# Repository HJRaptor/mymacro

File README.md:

# HackPad
## My experience
As part of **Hack Club’s HACKPAD YSWS** program, I embarked on a rewarding journey to build my own DIY macropad. This experience allowed me to explore various technical disciplines, from designing a custom **PCB in KiCAD** to **coding my very own firmware with QMK**. The most challenging aspect of the project was undoubtedly the PCB design. It required extensive research into component specifications, navigating datasheets, and ensuring that each part—switches, diodes, microcontrollers—was properly integrated into the design. The process of **placing components and routing the traces** was the most time-consuming and working through these challenges gave me a much deeper understanding of electronics design.

On the other hand, the part I enjoyed the most was **working with CAD**. With my existing CAD skills, I was able to confidently create a functional layout for the macropad’s physical structure. Translating these skills into real-world applications for a product I could use was fulfilling and rewarding. Coding the firmware was surprisingly straightforward, thanks to QMK's user-friendly environment, making the software side of things much simpler than anticipated. 
***Overall, this project was an invaluable learning experience that not only introduced me to PCB design but also allowed me to merge my existing skills with new knowledge to create something tangible and functional.***
## Bill Of Materials

    Xiao RP2040
    PCF8574 IO expander
    SSD1306 0.96 OLED
    (2) 4.7k resistor
    (16) SK6812 LED
    (16) 1N4148 diodes
    (16) Cherry MX brown switches

    (16) any keycaps at hq
    (16) Mill-Max 0305s hotswap socket
    (2) any encoder knobs at hq
    (2) EC11 encoder
    
    **--> Please laser cut the plate in 3mm clear acrylic and 3D print the rest of the pieces.**

### My Model

### My schematic

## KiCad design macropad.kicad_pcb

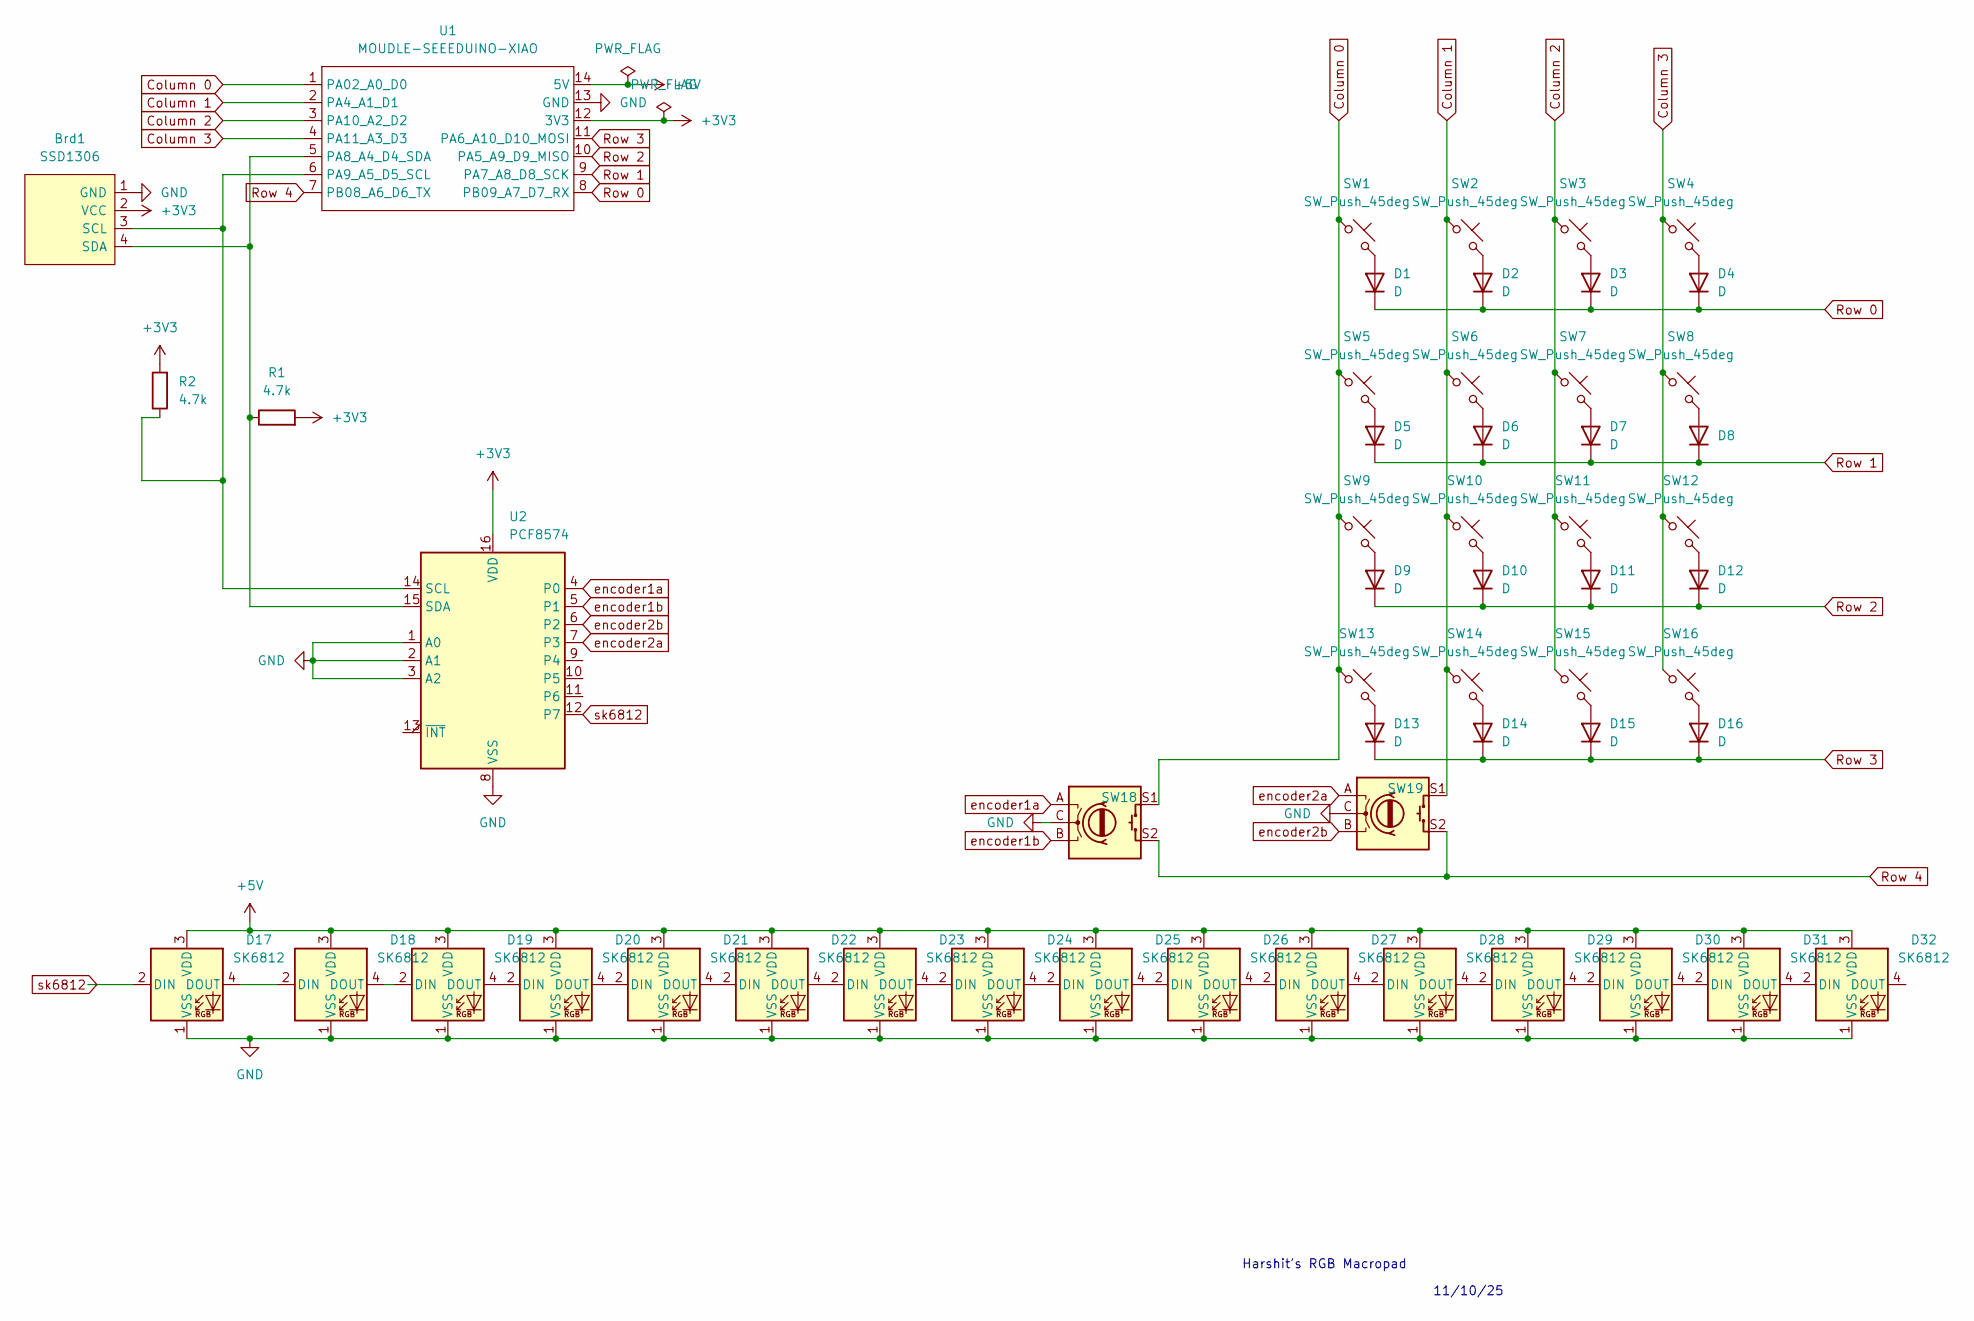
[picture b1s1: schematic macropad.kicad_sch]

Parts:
Brd1: SSD1306; SSD1306-0.91-OLED-4pin-128x32
D1, D2, D3, D4, D5, D6, D7, D8, D9, D10, D11, D12, D13, D14, D15, D16: D; D_DO-35_SOD27_P7.62mm_Horizontal
D17, D18, D19, D20, D21, D22, D23, D24, D25, D26, D27, D28, D29, D30, D31, D32: SK6812; LED_SK6812_PLCC4_5.0x5.0mm_P3.2mm
R1, R2: 4.7k; R_Axial_DIN0204_L3.6mm_D1.6mm_P5.08mm_Horizontal
SW1, SW2, SW3, SW4, SW5, SW6, SW7, SW8, SW9, SW10, SW11, SW12, SW13, SW14, SW15, SW16: SW_Push_45deg; SW_Cherry_MX_1.00u_PCB
SW18, SW19: RotaryEncoder_Switch; RotaryEncoder_Alps_EC11E-Switch_Vertical_H20mm
U1: MOUDLE-SEEEDUINO-XIAO; MOUDLE14P-2.54-21X17.8MM
U2: PCF8574; N16

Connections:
+3V3: Brd1.2 (VCC), R1.2, R2.2, U1.12 (3V3), U2.16 (VDD)
+5V: D17.3 (VDD), D18.3 (VDD), D19.3 (VDD), D20.3 (VDD), D21.3 (VDD), D22.3 (VDD), D23.3 (VDD), D24.3 (VDD), D25.3 (VDD), D26.3 (VDD), D27.3 (VDD), D28.3 (VDD), D29.3 (VDD), D30.3 (VDD), D31.3 (VDD), D32.3 (VDD), U1.14 (5V)
Column 0: SW1.1, SW5.1, SW9.1, SW13.1, SW18.S1, U1.1 (PA02_A0_D0)
Column 1: SW2.1, SW6.1, SW10.1, SW14.1, SW19.S1, U1.2 (PA4_A1_D1)
Column 2: SW3.1, SW7.1, SW11.1, SW15.1, U1.3 (PA10_A2_D2)
Column 3: SW4.1, SW8.1, SW12.1, SW16.1, U1.4 (PA11_A3_D3)
GND: Brd1.1 (GND), D17.1 (VSS), D18.1 (VSS), D19.1 (VSS), D20.1 (VSS), D21.1 (VSS), D22.1 (VSS), D23.1 (VSS), D24.1 (VSS), D25.1 (VSS), D26.1 (VSS), D27.1 (VSS), D28.1 (VSS), D29.1 (VSS), D30.1 (VSS), D31.1 (VSS), D32.1 (VSS), SW18.C, SW19.C, U1.13 (GND), U2.1 (A0), U2.2 (A1), U2.3 (A2), U2.8 (VSS)
unnamed: Brd1.3 (SCL), R2.1, U1.6 (PA9_A5_D5_SCL), U2.14 (SCL)
unnamed: Brd1.4 (SDA), R1.1, U1.5 (PA8_A4_D4_SDA), U2.15 (SDA)
unnamed: D1.2 (A), SW1.2
unnamed: D2.2 (A), SW2.2
unnamed: D3.2 (A), SW3.2
unnamed: D4.2 (A), SW4.2
unnamed: D5.2 (A), SW5.2
unnamed: D6.2 (A), SW6.2
unnamed: D7.2 (A), SW7.2
unnamed: D8.2 (A), SW8.2
unnamed: D9.2 (A), SW9.2
unnamed: D10.2 (A), SW10.2
unnamed: D11.2 (A), SW11.2
unnamed: D12.2 (A), SW12.2
unnamed: D13.2 (A), SW13.2
unnamed: D14.2 (A), SW14.2
unnamed: D15.2 (A), SW15.2
unnamed: D16.2 (A), SW16.2
unnamed: D17.4 (DOUT), D18.2 (DIN)
unnamed: D18.4 (DOUT), D19.2 (DIN)
unnamed: D19.4 (DOUT), D20.2 (DIN)
unnamed: D20.4 (DOUT), D21.2 (DIN)
unnamed: D21.4 (DOUT), D22.2 (DIN)
unnamed: D22.4 (DOUT), D23.2 (DIN)
unnamed: D23.4 (DOUT), D24.2 (DIN)
unnamed: D24.4 (DOUT), D25.2 (DIN)
unnamed: D25.4 (DOUT), D26.2 (DIN)
unnamed: D26.4 (DOUT), D27.2 (DIN)
unnamed: D27.4 (DOUT), D28.2 (DIN)
unnamed: D28.4 (DOUT), D29.2 (DIN)
unnamed: D29.4 (DOUT), D30.2 (DIN)
unnamed: D30.4 (DOUT), D31.2 (DIN)
unnamed: D31.4 (DOUT), D32.2 (DIN)
Row 0: D1.1 (K), D2.1 (K), D3.1 (K), D4.1 (K), U1.8 (PB09_A7_D7_RX)
Row 1: D5.1 (K), D6.1 (K), D7.1 (K), D8.1 (K), U1.9 (PA7_A8_D8_SCK)
Row 2: D9.1 (K), D10.1 (K), D11.1 (K), D12.1 (K), U1.10 (PA5_A9_D9_MISO)
Row 3: D13.1 (K), D14.1 (K), D15.1 (K), D16.1 (K), U1.11 (PA6_A10_D10_MOSI)
Row 4: SW18.S2, SW19.S2, U1.7 (PB08_A6_D6_TX)
encoder1a: SW18.A, U2.4 (P0)
encoder1b: SW18.B, U2.5 (P1)
encoder2a: SW19.A, U2.7 (P3)
encoder2b: SW19.B, U2.6 (P2)
sk6812: D17.2 (DIN), U2.12 (P7)

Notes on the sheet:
11/10/25
Harshit's RGB Macropad

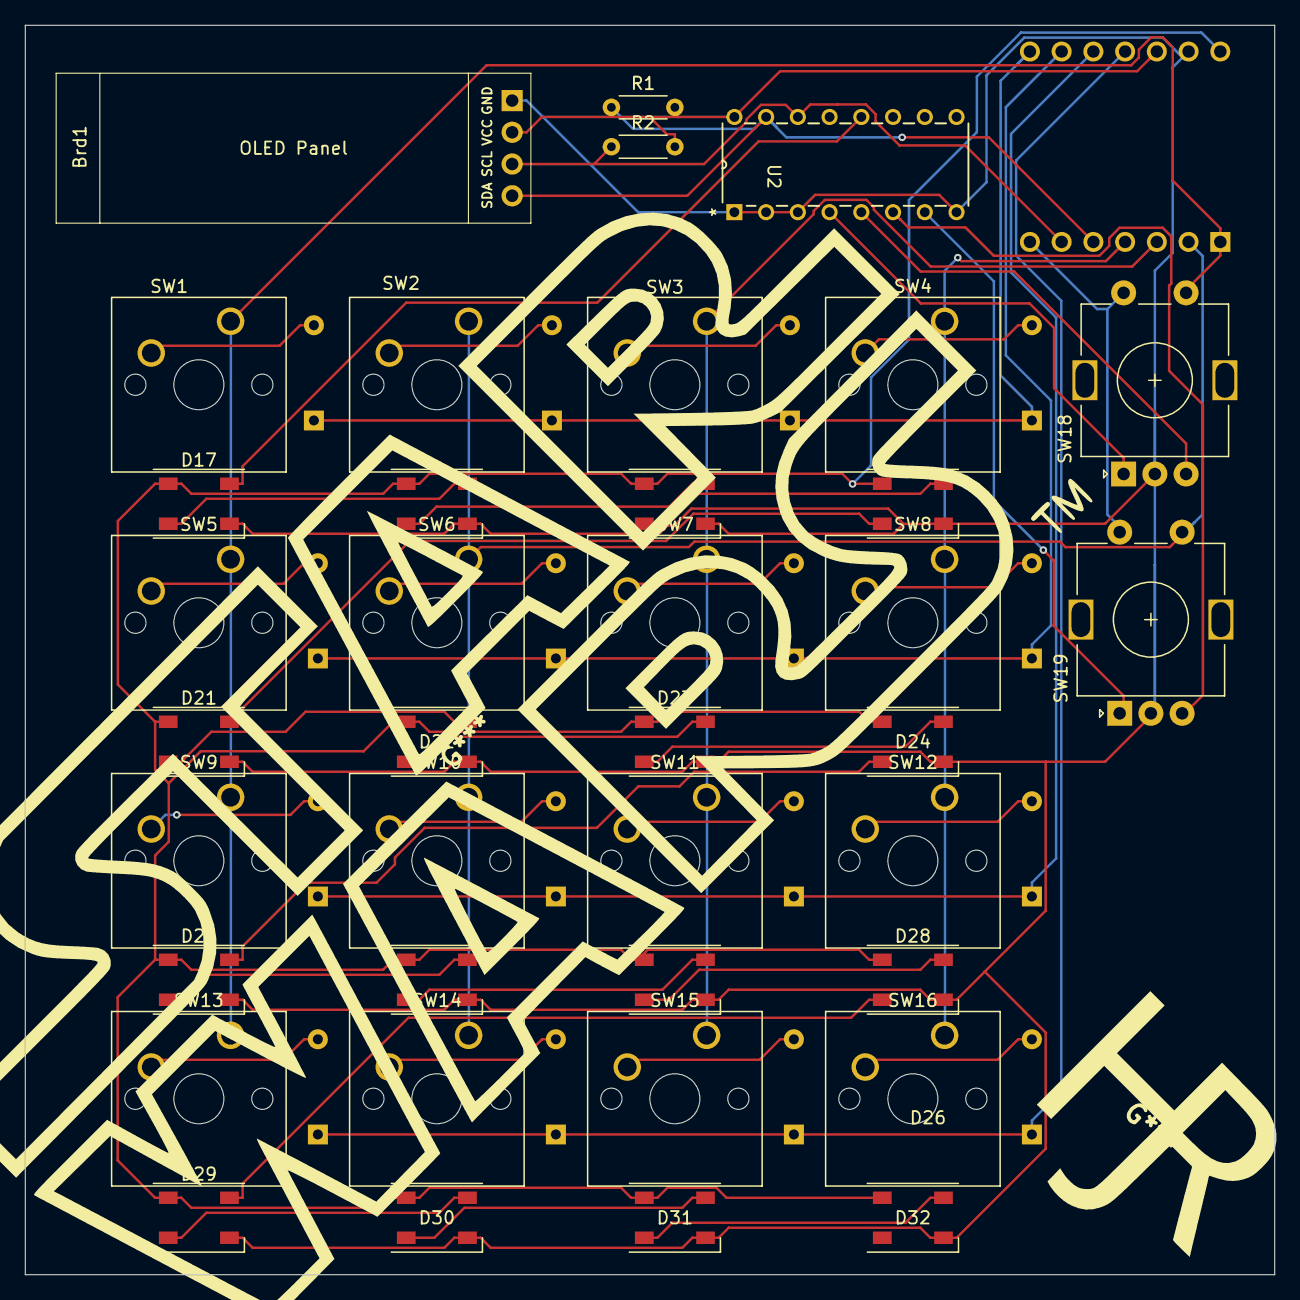
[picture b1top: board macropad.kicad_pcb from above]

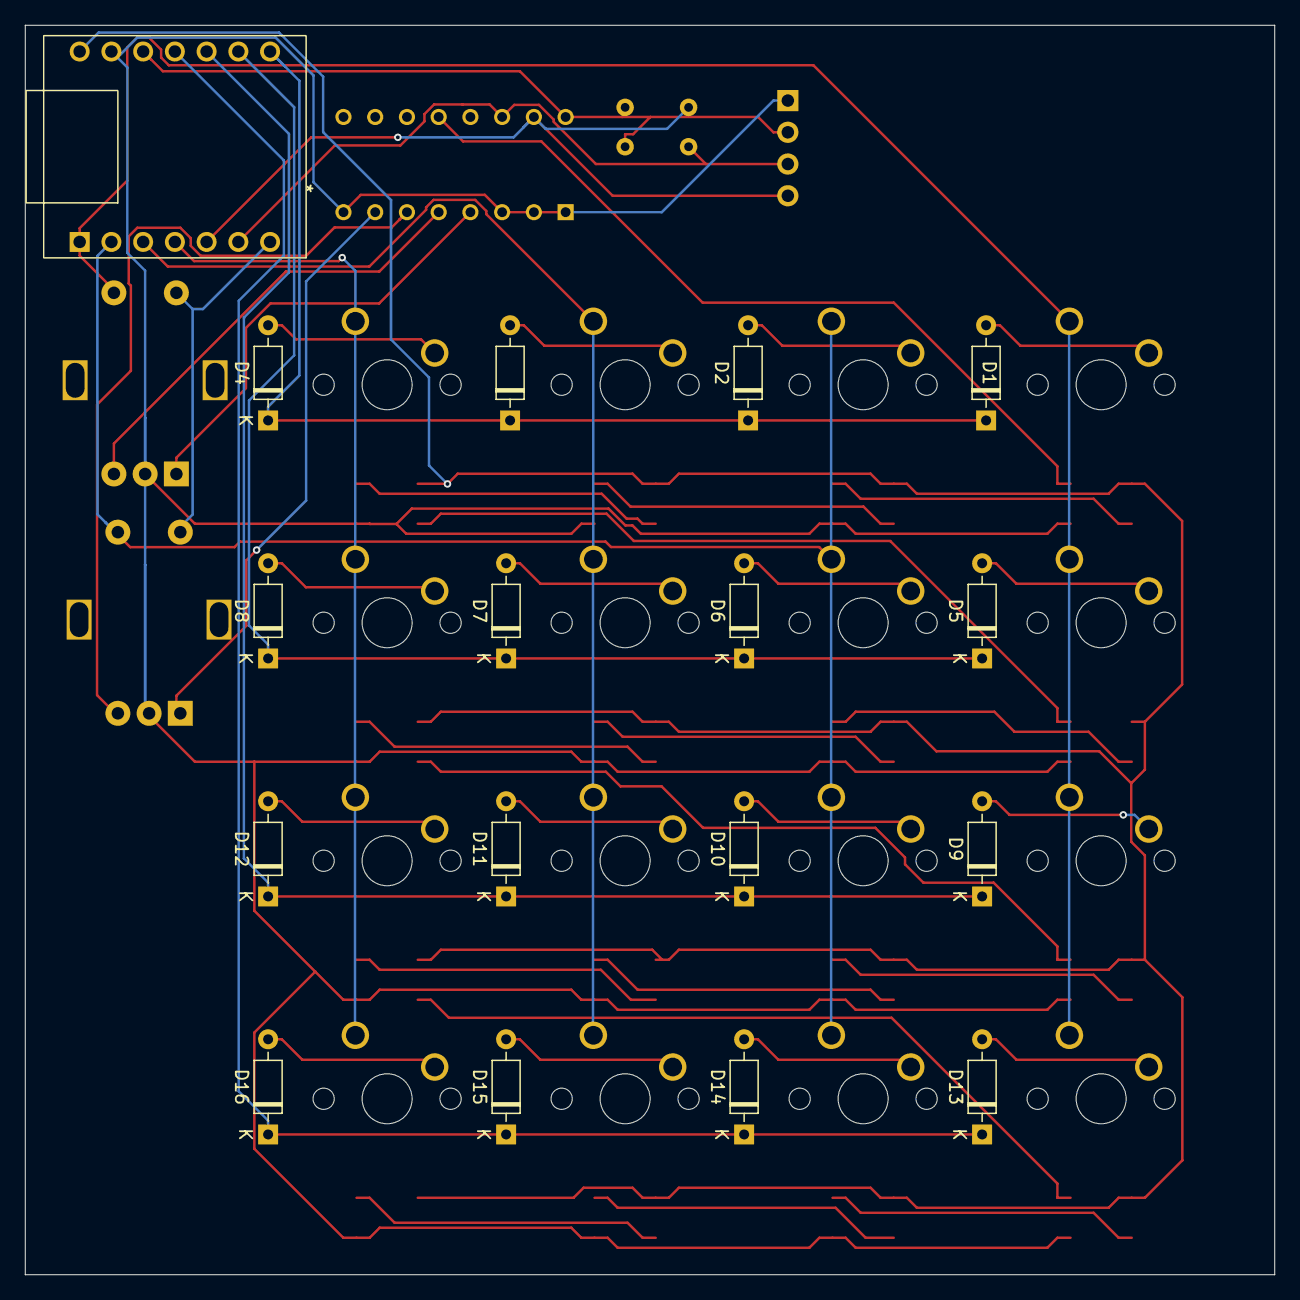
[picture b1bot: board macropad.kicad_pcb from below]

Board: 2 copper layers, 100.0 x 100.0 mm, 55 parts (17 on the bottom side), 50 nets.

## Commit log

2024-10-19 Add cad and firmware
2024-10-19 Uploading rest of the files
2024-10-19 update files
2024-10-19 update dxf
2024-10-20 edit README
